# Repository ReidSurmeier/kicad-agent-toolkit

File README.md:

# KiCad Agent Toolkit

Portable Codex skills, an audited KiCad MCP fork, engineering references, and
deterministic checks for evidence-driven KiCad design and fabrication review.

This repository turns one successful ten-key macropad redesign into a reusable
workflow. It does **not** claim that ERC, DRC, rendering, or Gerber parsing proves
that a circuit works. A design becomes functionally verified only after the
documented physical bring-up tests pass.

## Included skills

- `kicad-pcb-design`: study, capture, place, route, and verify KiCad projects.
- `kicad-design-review`: independently audit source and manufacturing packages.
- `kicad-toolchain-setup`: install and diagnose the portable CLI/MCP toolchain.

## Repository map

- `skills/`: installable Codex skills and their progressive-disclosure references.
- `docs/curriculum/`: source hierarchy and design-study curriculum.
- `docs/sources/`: claim-to-source comparison and redistribution policy.
- `docs/case-studies/`: lessons extracted from the ten-key USB-C board.
- `examples/tenkey-macropad/`: sanitized design evidence and selected source files.
- `pcb-agent`: one public CLI for install, diagnosis, validation, MCP testing,
  release generation, and supplemental external DFM analysis.
- `vendor/KiCAD-MCP-Server/`: pinned submodule for the audited MCP fork.
- `toolchain.lock.json`: exact revisions, container digests, versions, licenses,
  audit counts, and upstream test evidence.
- `Dockerfile` and `compose.yaml`: sandboxed, reproducible release environment.
- `tests/`: public-interface tests for the pipeline.

## Install on another machine

Clone with submodules, inspect the plan, then install:

```bash
git clone --recurse-submodules https://github.com/ReidSurmeier/kicad-agent-toolkit.git
cd kicad-agent-toolkit
./pcb-agent install --dry-run
./pcb-agent install
./pcb-agent doctor
./pcb-agent validate
./pcb-agent mcp test
```

The installer respects `CODEX_HOME`; when it is unset, it uses `~/.codex`.
Machine credentials belong in environment variables or an OS keychain. This
repository contains no JLCPCB keys, GitHub tokens, or personal absolute paths.

## Release a project

```bash
./pcb-agent release /path/to/Board.kicad_pro
```

This bundled release profile is intentionally JLCPCB-style and requires a
project `.kibot.yaml`. It is not a universal manufacturer profile. Add and test
a supplier-specific profile for another fabricator; do not just rename the ZIP.

The default gate runs whole-project ERC and DRC, exports fabrication and
assembly files, renders both PCB sides, parses every Gerber with PyGerber,
parses the complete Gerber/drill set with Gerbv, runs the project `.kibot.yaml`
in the digest-pinned container, verifies the ZIP CRC, hashes the evidence, and
proves that the source files did not change. If `firmware/qmk/*/keyboard.json`
is present, it also compiles the default keymap against the pinned QMK checkout
and AVR toolchain. The upload artifact is
`outputs/release/<project>/fabrication/<project>-JLCPCB.zip`.

## Run supplemental external DFM

Generate the fabrication archive first, then explicitly authorize its upload to
NextPCB HQDFM Online:

```bash
./pcb-agent dfm outputs/release/Board/fabrication/Board-JLCPCB.zip \
  --allow-upload --browser-backend local
```

For unattended runs, inject `BROWSERBASE_API_KEY` from a user-owned secret
wrapper and select `--browser-backend browserbase`. The key is inherited by the
runner and is never written to the report. The command uploads through the
provider's normal public web interface, downloads and parses the PDF, records
source and report hashes, and returns nonzero if the report has findings or
cannot be interpreted. Browserbase's temporary report download is deleted after
local retrieval.

This does not bypass JLCPCB API approval. JLCDFM's public page uses an ordinary
JLCPCB account session; the toolkit does not replay private endpoints or evade
that login. HQDFM is the supported no-login alternative and remains an
independent supplemental check, not JLCPCB process approval or proof of physical
function. Review the fabrication data and the provider's current data terms
before using `--allow-upload`.

To run the entire release in a container, place the project directory in
`PCB_PROJECT_DIR` and its project filename in `PCB_PROJECT_FILE`:

```bash
PCB_PROJECT_DIR=/path/to/project PCB_PROJECT_FILE=Board.kicad_pro docker compose run --rm pcb-agent
```

See [the full pipeline](docs/toolchain.md) for installation branches, MCP,
Browserbase and JLCPCB credential boundaries, release/DFM evidence, CI,
GitNexus, and limitations.

## Evidence policy

Use the exact component datasheet, errata, interface specification, official
reference circuit, selected fabricator capabilities, and authoritative KiCad
output for the design being reviewed. Textbooks and community boards are
learning and comparison material, not substitutes for controlling sources.

See [the curriculum](docs/curriculum/design-study.md), [source comparison](docs/sources/comparison.md),
and [TenKey case study](docs/case-studies/tenkey-macropad.md).

## License

Code and original documentation are MIT licensed. Third-party documents and
designs remain under their own licenses and are represented by citations or
metadata unless redistribution is explicitly permitted.

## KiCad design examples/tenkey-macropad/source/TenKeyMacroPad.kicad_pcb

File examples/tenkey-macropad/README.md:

# TenKey macropad evidence fixture

This directory contains the sanitized KiCad source and engineering records used
to exercise the toolkit. It is a design-checks-passed case study, not a certified
reference design or proof of assembled hardware.

- `source/`: KiCad project, project rules, jobset, KiBot configuration, and local
  custom footprint.
- `docs/`: requirements research, calculations, decisions, assembly/fabrication
  notes, verification record, and the unexecuted bring-up plan.
- `design/`: machine-readable request, evidence, and firmware pin contract.
- `qa/`: release-gate contract.

The USB-C connector is GCT USB4085-GF-A, a through-hole part requiring a later
THT soldering step. All SMT is on the underside; the ten MX switches mount from
the user side.

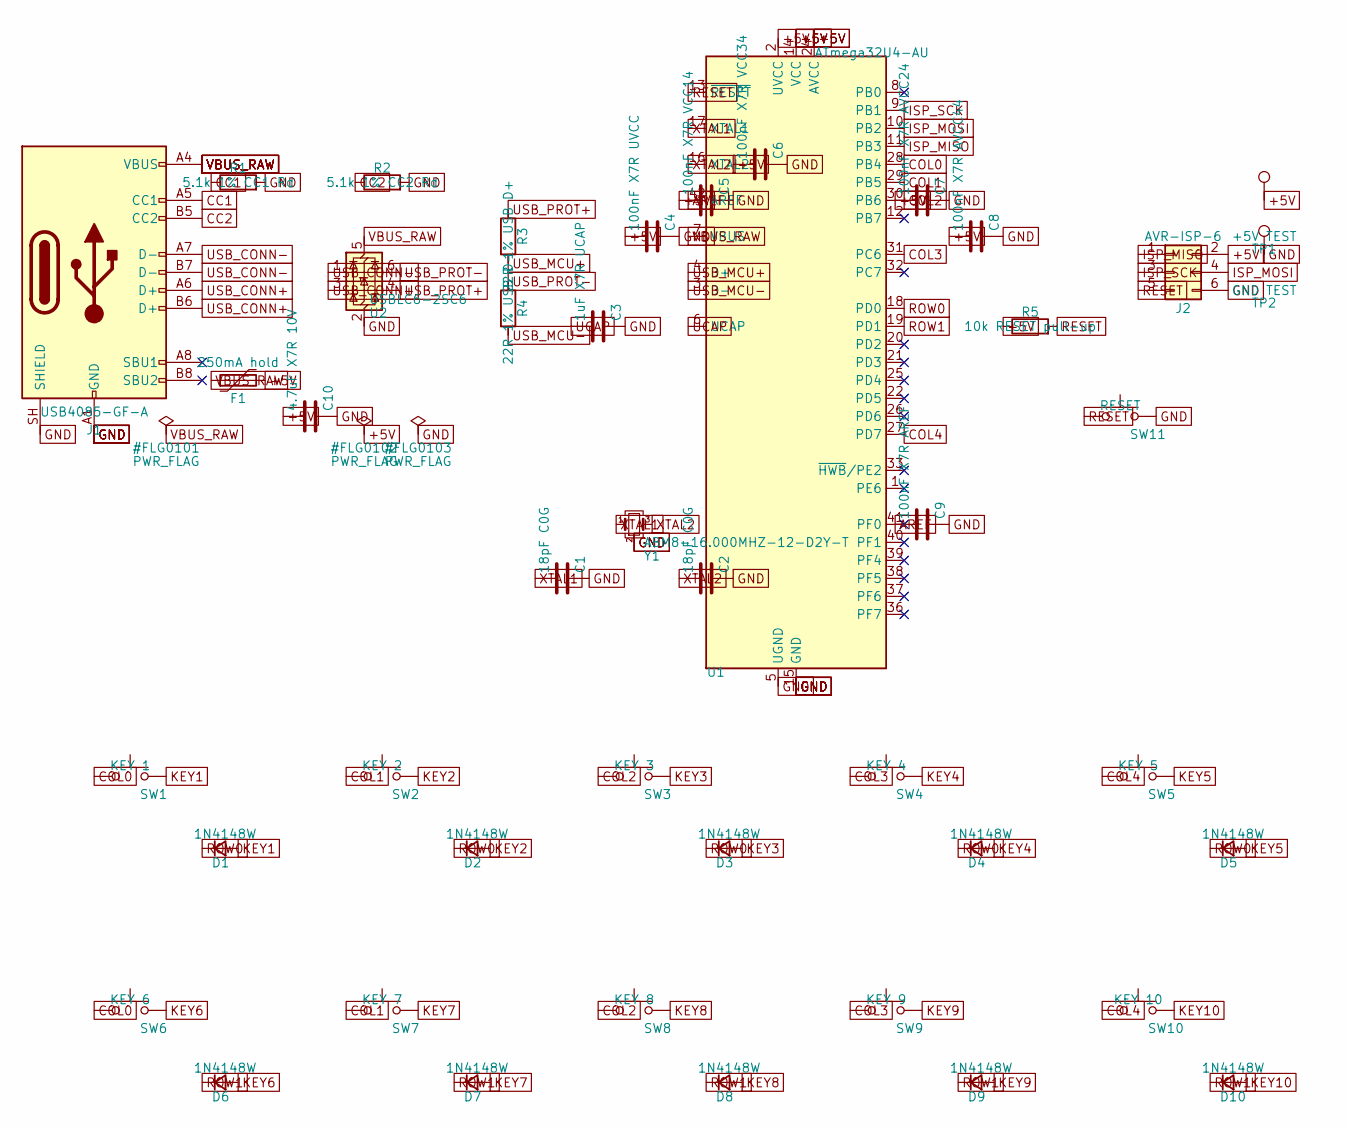
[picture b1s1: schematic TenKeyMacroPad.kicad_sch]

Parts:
C1, C2: 18pF C0G; C_0603_1608Metric
C3: 1uF X7R UCAP; C_0603_1608Metric
C4: 100nF X7R UVCC; C_0603_1608Metric
C5: 100nF X7R VCC14; C_0603_1608Metric
C6: 100nF X7R VCC34; C_0603_1608Metric
C7: 100nF X7R AVCC24; C_0603_1608Metric
C8: 100nF X7R AVCC44; C_0603_1608Metric
C9: 100nF X7R AREF; C_0603_1608Metric
C10: 4.7uF X7R 10V; C_0805_2012Metric
D1, D2, D3, D4, D5, D6, D7, D8, D9, D10: 1N4148W; D_SOD-123
F1: 250mA hold; PTC_1206_3216Metric
J1: USB4085-GF-A; USB_C_Receptacle_GCT_USB4085; MPN USB4085-GF-A; LCSC C7095263
J2: AVR-ISP-6; PinHeader_2x03_P2.54mm_Vertical
R1: 5.1k 1% CC1 Rd; R_0603_1608Metric
R2: 5.1k 1% CC2 Rd; R_0603_1608Metric
R3: 22R 1% USB D+; R_0603_1608Metric
R4: 22R 1% USB D-; R_0603_1608Metric
R5: 10k RESET pull-up; R_0603_1608Metric
SW1: KEY 1; SW_Cherry_MX_1.00u_PCB
SW2: KEY 2; SW_Cherry_MX_1.00u_PCB
SW3: KEY 3; SW_Cherry_MX_1.00u_PCB
SW4: KEY 4; SW_Cherry_MX_1.00u_PCB
SW5: KEY 5; SW_Cherry_MX_1.00u_PCB
SW6: KEY 6; SW_Cherry_MX_1.00u_PCB
SW7: KEY 7; SW_Cherry_MX_1.00u_PCB
SW8: KEY 8; SW_Cherry_MX_1.00u_PCB
SW9: KEY 9; SW_Cherry_MX_1.00u_PCB
SW10: KEY 10; SW_Cherry_MX_1.00u_PCB
SW11: RESET; SW_SPST_SKQG_WithoutStem
TP1: +5V TEST; TestPoint_Pad_D1.0mm
TP2: GND TEST; TestPoint_Pad_D1.0mm
U1: ATmega32U4-AU; TQFP-44_10x10mm_P0.8mm
U2: USBLC6-2SC6; SOT-23-6
Y1: ABM8-16.000MHZ-12-D2Y-T; Crystal_SMD_3225-4Pin_3.2x2.5mm

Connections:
+5V: C4.1, C5.1, C6.1, C7.1, C8.1, C10.1, F1.2, J2.2, R5.1, TP1.1, U1.2 (UVCC), U1.14 (VCC), U1.24 (AVCC), U1.34 (VCC), U1.44 (AVCC)
AREF: C9.1, U1.42 (AREF)
CC1: J1.A5 (CC1), R1.1
CC2: J1.B5 (CC2), R2.1
COL0: SW1.1, SW6.1, U1.28 (PB4)
COL1: SW2.1, SW7.1, U1.29 (PB5)
COL2: SW3.1, SW8.1, U1.30 (PB6)
COL3: SW4.1, SW9.1, U1.31 (PC6)
COL4: SW5.1, SW10.1, U1.27 (PD7)
GND: C1.2, C2.2, C3.2, C4.2, C5.2, C6.2, C7.2, C8.2, C9.2, C10.2, J1.A1 (GND), J1.A12 (GND), J1.B1 (GND), J1.B12 (GND), J1.SH (SHIELD), J2.6, R1.2, R2.2, SW11.2, TP2.1, U1.5 (UGND), U1.15 (GND), U1.23 (GND), U1.35 (GND), U1.43 (GND), U2.2 (GND), Y1.2 (G), Y1.4 (G)
ISP_MISO: J2.1, U1.11 (PB3)
ISP_MOSI: J2.4, U1.10 (PB2)
ISP_SCK: J2.3, U1.9 (PB1)
KEY1: D1.2 (A), SW1.2
KEY2: D2.2 (A), SW2.2
KEY3: D3.2 (A), SW3.2
KEY4: D4.2 (A), SW4.2
KEY5: D5.2 (A), SW5.2
KEY6: D6.2 (A), SW6.2
KEY7: D7.2 (A), SW7.2
KEY8: D8.2 (A), SW8.2
KEY9: D9.2 (A), SW9.2
KEY10: D10.2 (A), SW10.2
RESET: J2.5, R5.2, SW11.1, U1.13 (~RESET)
ROW0: D1.1 (K), D2.1 (K), D3.1 (K), D4.1 (K), D5.1 (K), U1.18 (PD0)
ROW1: D6.1 (K), D7.1 (K), D8.1 (K), D9.1 (K), D10.1 (K), U1.19 (PD1)
UCAP: C3.1, U1.6 (UCAP)
USB_CONN+: J1.A6 (D+), J1.B6 (D+), U2.3 (I/O2)
USB_CONN-: J1.A7 (D-), J1.B7 (D-), U2.1 (I/O1)
USB_MCU+: R3.2, U1.4 (D+)
USB_MCU-: R4.2, U1.3 (D-)
USB_PROT+: R3.1, U2.4 (I/O2)
USB_PROT-: R4.1, U2.6 (I/O1)
VBUS_RAW: F1.1, J1.A4 (VBUS), J1.A9 (VBUS), J1.B4 (VBUS), J1.B9 (VBUS), U1.7 (VBUS), U2.5 (VBUS)
XTAL1: C1.1, U1.17 (XTAL1), Y1.1
XTAL2: C2.1, U1.16 (XTAL2), Y1.3

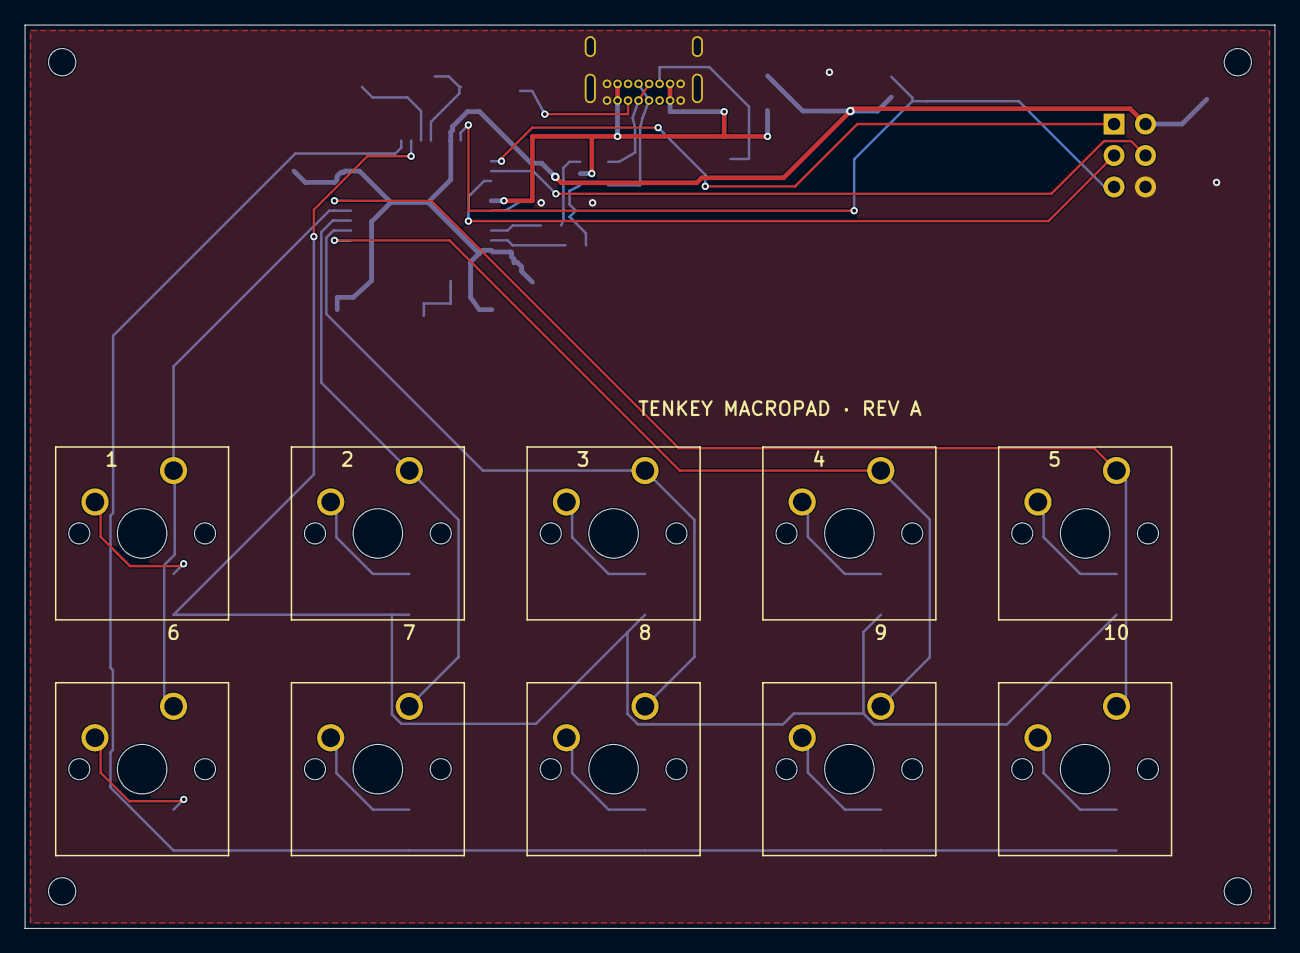
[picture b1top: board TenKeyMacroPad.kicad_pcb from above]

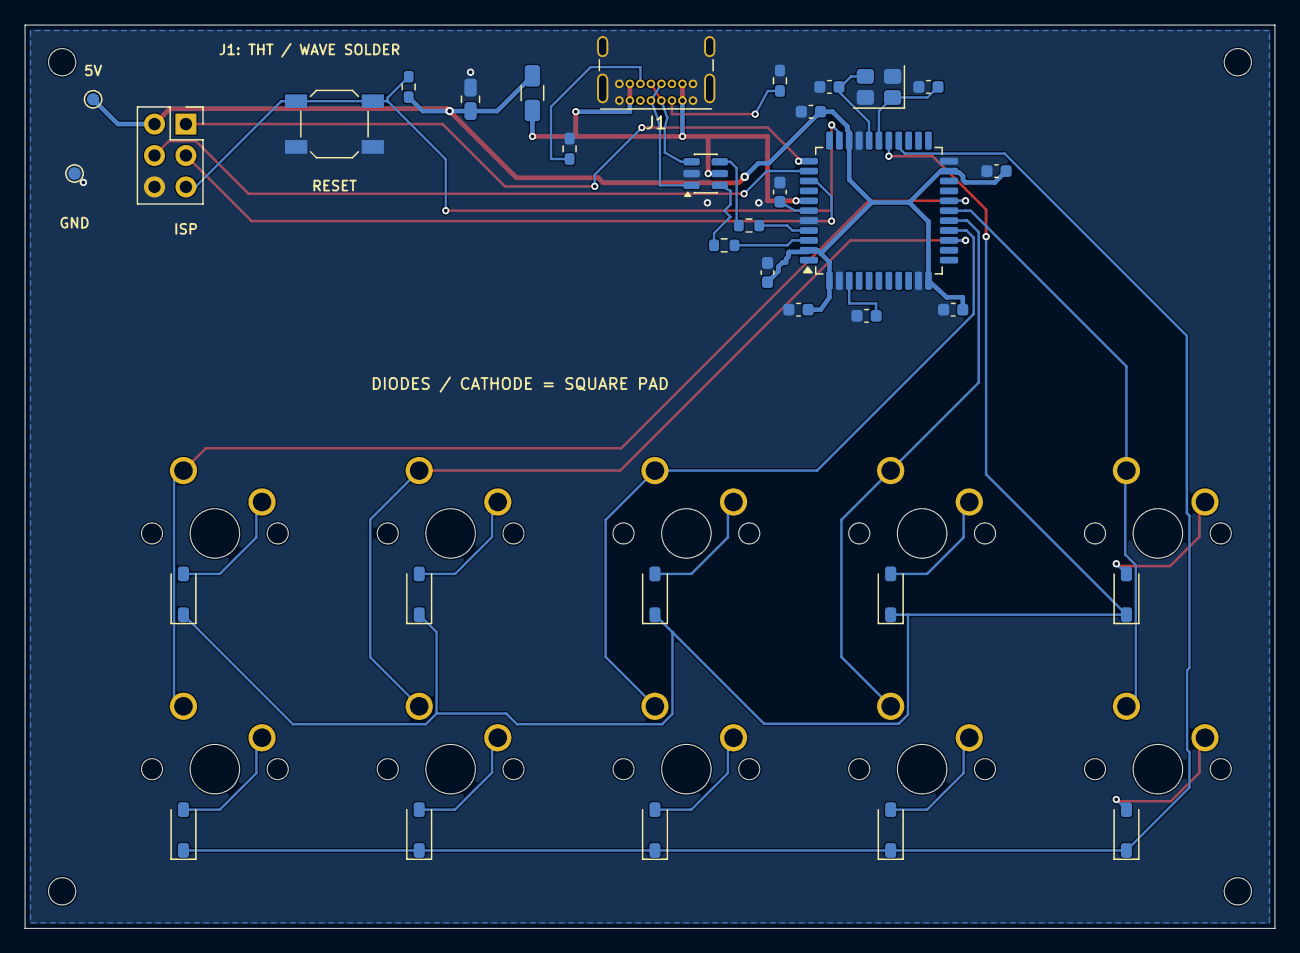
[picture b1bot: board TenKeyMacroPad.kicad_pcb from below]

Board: 2 copper layers, 101.0 x 73.0 mm, 48 parts (34 on the bottom side), 36 nets.

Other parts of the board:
H1, H2, H3, H4: M2; MountingHole_2.2mm_M2
